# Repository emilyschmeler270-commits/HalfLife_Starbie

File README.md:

#My Starbie :D

I am so so happy to be making this project! Starboy actually inspired me recently to learn hardware and coding, so for my first project to be inspired by it is awesome!

##What it is

Its like a keychain pet that reacts to the environment around you. It has its own personality and is just super cute!!

##Why I am making it

I am making it for the first week of Hack-Club Half-Life (and also because I've always wanted a keycahin pet).

#Project Status

Still figuring everything out, definitely not very great with the new software or writing READMEs (never written a full on before) so hopefully I will get the hang of it by the end of this course. :D

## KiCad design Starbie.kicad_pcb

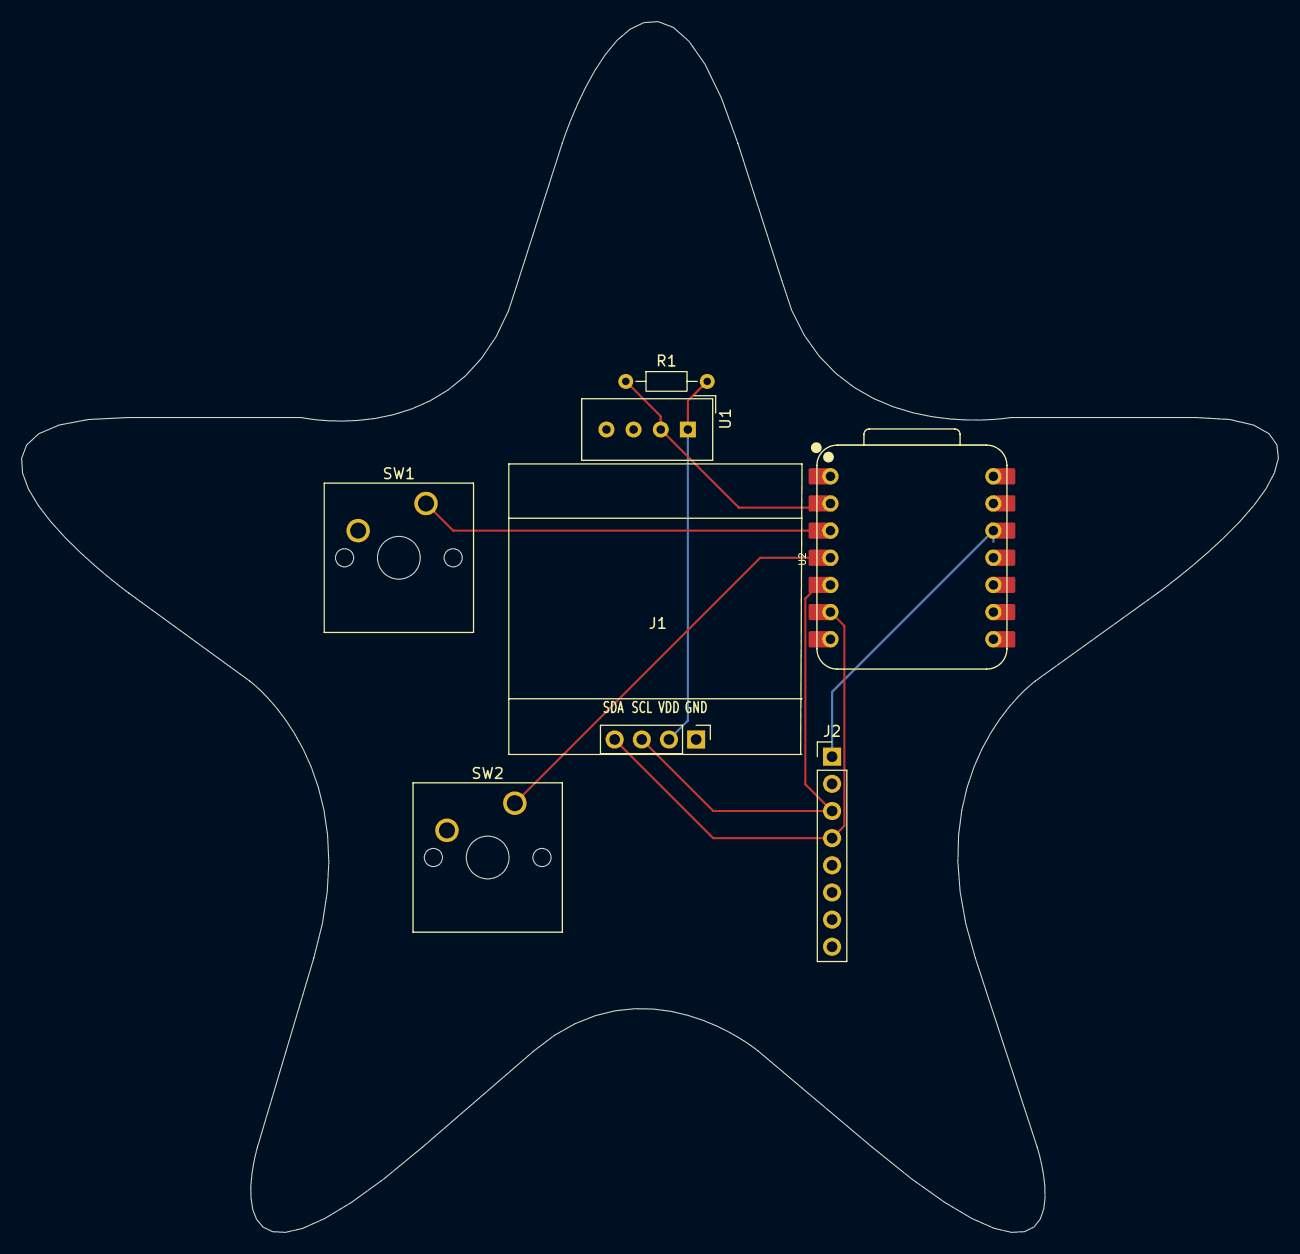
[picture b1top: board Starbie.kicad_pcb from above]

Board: 2 copper layers, 117.6 x 113.3 mm, 7 parts (0 on the bottom side), 7 nets.

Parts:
J1: Conn_01x04_Pin; Display_128x64_096_I2C
J2: Conn_01x08_Pin; PinHeader_1x08_P2.54mm_Vertical
R1: 10k; R_Axial_DIN0204_L3.6mm_D1.6mm_P7.62mm_Horizontal
SW1, SW2: SW_Push; SW_Cherry_MX_1.00u_PCB
U1: DHT11; Aosong_DHT11_5.5x12.0_P2.54mm
U2: XIAO-ESP32-C3-SMD; XIAO-ESP32-C6-DIP

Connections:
+3.3V: J1.2, J2.1, R1.2, U1.1 (VDD), U2.12 (3V3_OUT)
/DHT11 DATA: R1.1, U1.2 (DATA), U2.2 (D1)
/GPI02: SW1.1, U2.3 (D2)
/GPI03: SW2.1, U2.4 (D3)
/SCL: J1.3, J2.3, U2.5 (D4)
/SDA: J1.4, J2.4, U2.6 (D5)
GND: J1.1, J2.2, SW1.2, SW2.2, U1.4 (GND), U2.13 (GND)
